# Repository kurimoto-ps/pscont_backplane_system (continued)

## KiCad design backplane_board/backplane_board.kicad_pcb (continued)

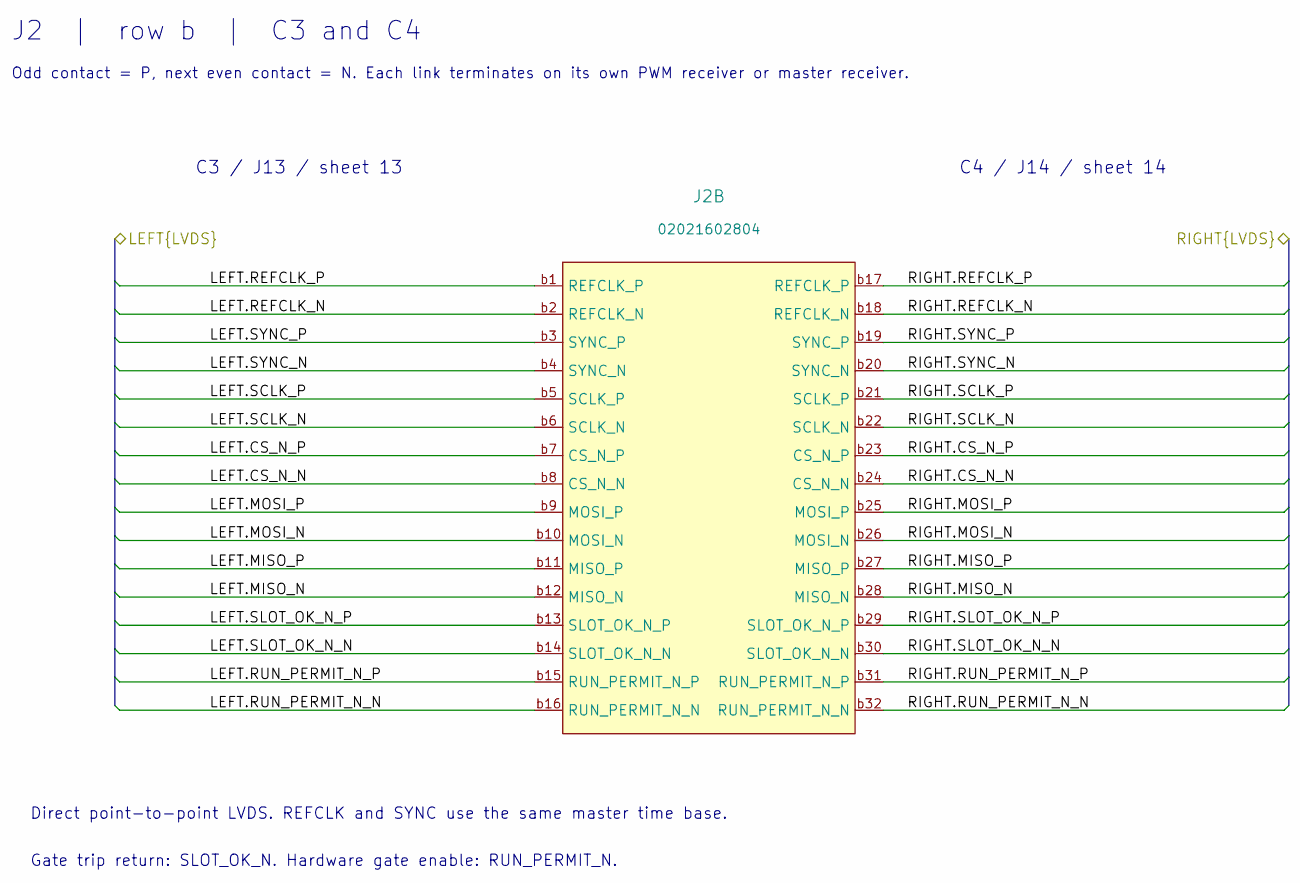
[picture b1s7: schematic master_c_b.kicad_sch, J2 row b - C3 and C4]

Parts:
J2: 02021602804; HARBUS64_02021602804; MPN 02021602804

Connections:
/C3.CS_N_N: J2.b8 (CS_N_N); also elsewhere on the board
/C3.CS_N_P: J2.b7 (CS_N_P); also elsewhere on the board
/C3.MISO_N: J2.b12 (MISO_N); also elsewhere on the board
/C3.MISO_P: J2.b11 (MISO_P); also elsewhere on the board
/C3.MOSI_N: J2.b10 (MOSI_N); also elsewhere on the board
/C3.MOSI_P: J2.b9 (MOSI_P); also elsewhere on the board
/C3.REFCLK_N: J2.b2 (REFCLK_N); also elsewhere on the board
/C3.REFCLK_P: J2.b1 (REFCLK_P); also elsewhere on the board
/C3.RUN_PERMIT_N_N: J2.b16 (RUN_PERMIT_N_N); also elsewhere on the board
/C3.RUN_PERMIT_N_P: J2.b15 (RUN_PERMIT_N_P); also elsewhere on the board
/C3.SCLK_N: J2.b6 (SCLK_N); also elsewhere on the board
/C3.SCLK_P: J2.b5 (SCLK_P); also elsewhere on the board
/C3.SLOT_OK_N_N: J2.b14 (SLOT_OK_N_N); also elsewhere on the board
/C3.SLOT_OK_N_P: J2.b13 (SLOT_OK_N_P); also elsewhere on the board
/C3.SYNC_N: J2.b4 (SYNC_N); also elsewhere on the board
/C3.SYNC_P: J2.b3 (SYNC_P); also elsewhere on the board
/C4.CS_N_N: J2.b24 (CS_N_N); also elsewhere on the board
/C4.CS_N_P: J2.b23 (CS_N_P); also elsewhere on the board
/C4.MISO_N: J2.b28 (MISO_N); also elsewhere on the board
/C4.MISO_P: J2.b27 (MISO_P); also elsewhere on the board
/C4.MOSI_N: J2.b26 (MOSI_N); also elsewhere on the board
/C4.MOSI_P: J2.b25 (MOSI_P); also elsewhere on the board
/C4.REFCLK_N: J2.b18 (REFCLK_N); also elsewhere on the board
/C4.REFCLK_P: J2.b17 (REFCLK_P); also elsewhere on the board
/C4.RUN_PERMIT_N_N: J2.b32 (RUN_PERMIT_N_N); also elsewhere on the board
/C4.RUN_PERMIT_N_P: J2.b31 (RUN_PERMIT_N_P); also elsewhere on the board
/C4.SCLK_N: J2.b22 (SCLK_N); also elsewhere on the board
/C4.SCLK_P: J2.b21 (SCLK_P); also elsewhere on the board
/C4.SLOT_OK_N_N: J2.b30 (SLOT_OK_N_N); also elsewhere on the board
/C4.SLOT_OK_N_P: J2.b29 (SLOT_OK_N_P); also elsewhere on the board
/C4.SYNC_N: J2.b20 (SYNC_N); also elsewhere on the board
/C4.SYNC_P: J2.b19 (SYNC_P); also elsewhere on the board

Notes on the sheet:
J2 | row b | C3 and C4
Odd contact = P, next even contact = N. Each link terminates on its own PWM receiver or master receiver.
C3 / J13 / sheet 13
C4 / J14 / sheet 14
Direct point-to-point LVDS. REFCLK and SYNC use the same master time base.
Gate trip return: SLOT_OK_N. Hardware gate enable: RUN_PERMIT_N.

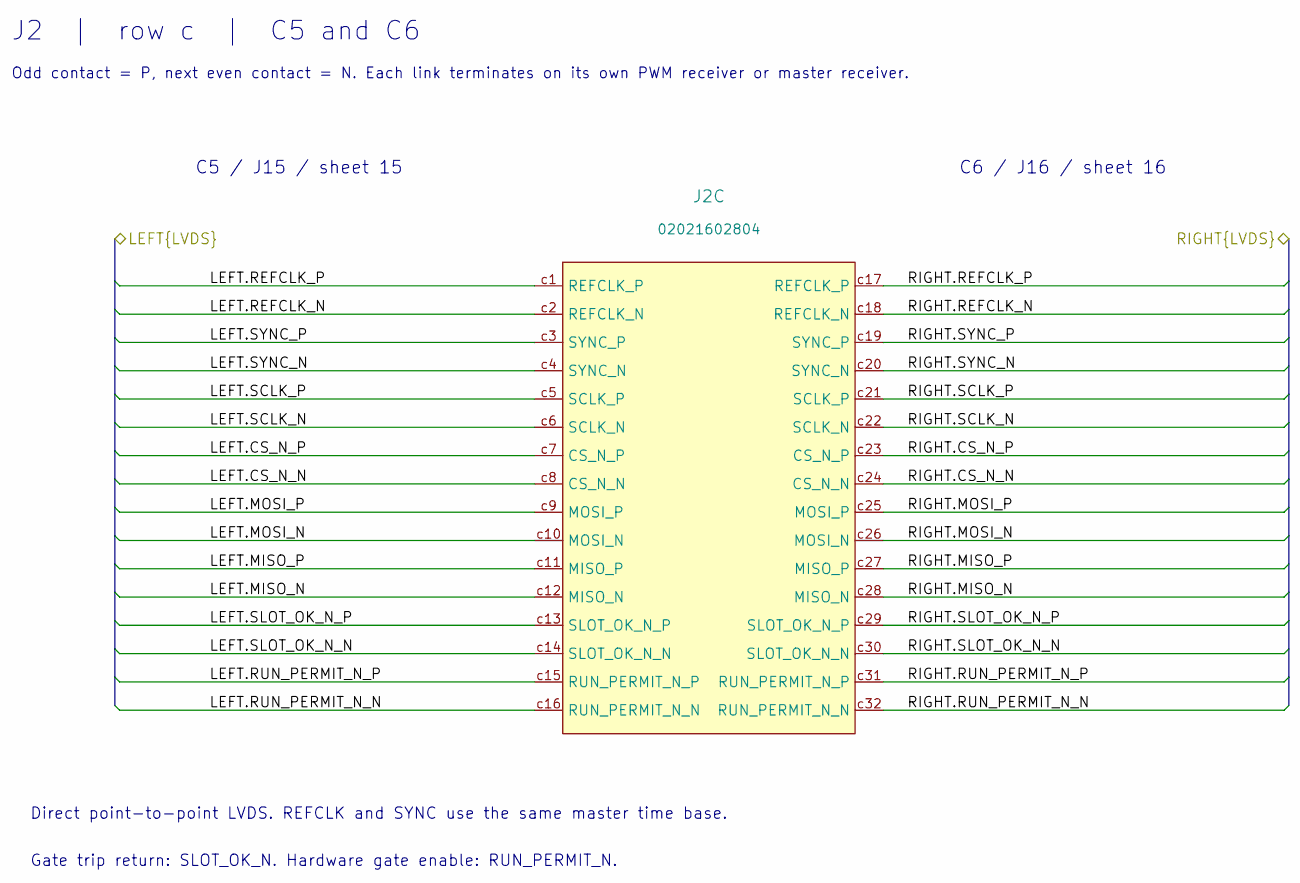
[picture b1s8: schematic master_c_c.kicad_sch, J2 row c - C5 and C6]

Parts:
J2: 02021602804; HARBUS64_02021602804; MPN 02021602804

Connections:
/C5.CS_N_N: J2.c8 (CS_N_N); also elsewhere on the board
/C5.CS_N_P: J2.c7 (CS_N_P); also elsewhere on the board
/C5.MISO_N: J2.c12 (MISO_N); also elsewhere on the board
/C5.MISO_P: J2.c11 (MISO_P); also elsewhere on the board
/C5.MOSI_N: J2.c10 (MOSI_N); also elsewhere on the board
/C5.MOSI_P: J2.c9 (MOSI_P); also elsewhere on the board
/C5.REFCLK_N: J2.c2 (REFCLK_N); also elsewhere on the board
/C5.REFCLK_P: J2.c1 (REFCLK_P); also elsewhere on the board
/C5.RUN_PERMIT_N_N: J2.c16 (RUN_PERMIT_N_N); also elsewhere on the board
/C5.RUN_PERMIT_N_P: J2.c15 (RUN_PERMIT_N_P); also elsewhere on the board
/C5.SCLK_N: J2.c6 (SCLK_N); also elsewhere on the board
/C5.SCLK_P: J2.c5 (SCLK_P); also elsewhere on the board
/C5.SLOT_OK_N_N: J2.c14 (SLOT_OK_N_N); also elsewhere on the board
/C5.SLOT_OK_N_P: J2.c13 (SLOT_OK_N_P); also elsewhere on the board
/C5.SYNC_N: J2.c4 (SYNC_N); also elsewhere on the board
/C5.SYNC_P: J2.c3 (SYNC_P); also elsewhere on the board
/C6.CS_N_N: J2.c24 (CS_N_N); also elsewhere on the board
/C6.CS_N_P: J2.c23 (CS_N_P); also elsewhere on the board
/C6.MISO_N: J2.c28 (MISO_N); also elsewhere on the board
/C6.MISO_P: J2.c27 (MISO_P); also elsewhere on the board
/C6.MOSI_N: J2.c26 (MOSI_N); also elsewhere on the board
/C6.MOSI_P: J2.c25 (MOSI_P); also elsewhere on the board
/C6.REFCLK_N: J2.c18 (REFCLK_N); also elsewhere on the board
/C6.REFCLK_P: J2.c17 (REFCLK_P); also elsewhere on the board
/C6.RUN_PERMIT_N_N: J2.c32 (RUN_PERMIT_N_N); also elsewhere on the board
/C6.RUN_PERMIT_N_P: J2.c31 (RUN_PERMIT_N_P); also elsewhere on the board
/C6.SCLK_N: J2.c22 (SCLK_N); also elsewhere on the board
/C6.SCLK_P: J2.c21 (SCLK_P); also elsewhere on the board
/C6.SLOT_OK_N_N: J2.c30 (SLOT_OK_N_N); also elsewhere on the board
/C6.SLOT_OK_N_P: J2.c29 (SLOT_OK_N_P); also elsewhere on the board
/C6.SYNC_N: J2.c20 (SYNC_N); also elsewhere on the board
/C6.SYNC_P: J2.c19 (SYNC_P); also elsewhere on the board

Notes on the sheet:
J2 | row c | C5 and C6
Odd contact = P, next even contact = N. Each link terminates on its own PWM receiver or master receiver.
C5 / J15 / sheet 15
C6 / J16 / sheet 16
Direct point-to-point LVDS. REFCLK and SYNC use the same master time base.
Gate trip return: SLOT_OK_N. Hardware gate enable: RUN_PERMIT_N.

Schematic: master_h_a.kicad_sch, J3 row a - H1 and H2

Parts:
J3: 02021602804; HARBUS64_02021602804; MPN 02021602804

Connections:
/H1.CS_N_N: J3.a8 (CS_N_N); also elsewhere on the board
/H1.CS_N_P: J3.a7 (CS_N_P); also elsewhere on the board
/H1.MISO_N: J3.a12 (MISO_N); also elsewhere on the board
/H1.MISO_P: J3.a11 (MISO_P); also elsewhere on the board
/H1.MOSI_N: J3.a10 (MOSI_N); also elsewhere on the board
/H1.MOSI_P: J3.a9 (MOSI_P); also elsewhere on the board
/H1.REFCLK_N: J3.a2 (REFCLK_N); also elsewhere on the board
/H1.REFCLK_P: J3.a1 (REFCLK_P); also elsewhere on the board
/H1.RUN_PERMIT_N_N: J3.a16 (RUN_PERMIT_N_N); also elsewhere on the board
/H1.RUN_PERMIT_N_P: J3.a15 (RUN_PERMIT_N_P); also elsewhere on the board
/H1.SCLK_N: J3.a6 (SCLK_N); also elsewhere on the board
/H1.SCLK_P: J3.a5 (SCLK_P); also elsewhere on the board
/H1.SLOT_OK_N_N: J3.a14 (SLOT_OK_N_N); also elsewhere on the board
/H1.SLOT_OK_N_P: J3.a13 (SLOT_OK_N_P); also elsewhere on the board
/H1.SYNC_N: J3.a4 (SYNC_N); also elsewhere on the board
/H1.SYNC_P: J3.a3 (SYNC_P); also elsewhere on the board
/H2.CS_N_N: J3.a24 (CS_N_N); also elsewhere on the board
/H2.CS_N_P: J3.a23 (CS_N_P); also elsewhere on the board
/H2.MISO_N: J3.a28 (MISO_N); also elsewhere on the board
/H2.MISO_P: J3.a27 (MISO_P); also elsewhere on the board
/H2.MOSI_N: J3.a26 (MOSI_N); also elsewhere on the board
/H2.MOSI_P: J3.a25 (MOSI_P); also elsewhere on the board
/H2.REFCLK_N: J3.a18 (REFCLK_N); also elsewhere on the board
/H2.REFCLK_P: J3.a17 (REFCLK_P); also elsewhere on the board
/H2.RUN_PERMIT_N_N: J3.a32 (RUN_PERMIT_N_N); also elsewhere on the board
/H2.RUN_PERMIT_N_P: J3.a31 (RUN_PERMIT_N_P); also elsewhere on the board
/H2.SCLK_N: J3.a22 (SCLK_N); also elsewhere on the board
/H2.SCLK_P: J3.a21 (SCLK_P); also elsewhere on the board
/H2.SLOT_OK_N_N: J3.a30 (SLOT_OK_N_N); also elsewhere on the board
/H2.SLOT_OK_N_P: J3.a29 (SLOT_OK_N_P); also elsewhere on the board
/H2.SYNC_N: J3.a20 (SYNC_N); also elsewhere on the board
/H2.SYNC_P: J3.a19 (SYNC_P); also elsewhere on the board

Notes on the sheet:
J3 | row a | H1 and H2
Odd contact = P, next even contact = N. Each link terminates on its own PWM receiver or master receiver.
H1 / J17 / sheet 17
H2 / J18 / sheet 18
Direct point-to-point LVDS. REFCLK and SYNC use the same master time base.
Gate trip return: SLOT_OK_N. Hardware gate enable: RUN_PERMIT_N.

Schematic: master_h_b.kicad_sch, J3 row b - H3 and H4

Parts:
J3: 02021602804; HARBUS64_02021602804; MPN 02021602804

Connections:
/H3.CS_N_N: J3.b8 (CS_N_N); also elsewhere on the board
/H3.CS_N_P: J3.b7 (CS_N_P); also elsewhere on the board
/H3.MISO_N: J3.b12 (MISO_N); also elsewhere on the board
/H3.MISO_P: J3.b11 (MISO_P); also elsewhere on the board
/H3.MOSI_N: J3.b10 (MOSI_N); also elsewhere on the board
/H3.MOSI_P: J3.b9 (MOSI_P); also elsewhere on the board
/H3.REFCLK_N: J3.b2 (REFCLK_N); also elsewhere on the board
/H3.REFCLK_P: J3.b1 (REFCLK_P); also elsewhere on the board
/H3.RUN_PERMIT_N_N: J3.b16 (RUN_PERMIT_N_N); also elsewhere on the board
/H3.RUN_PERMIT_N_P: J3.b15 (RUN_PERMIT_N_P); also elsewhere on the board
/H3.SCLK_N: J3.b6 (SCLK_N); also elsewhere on the board
/H3.SCLK_P: J3.b5 (SCLK_P); also elsewhere on the board
/H3.SLOT_OK_N_N: J3.b14 (SLOT_OK_N_N); also elsewhere on the board
/H3.SLOT_OK_N_P: J3.b13 (SLOT_OK_N_P); also elsewhere on the board
/H3.SYNC_N: J3.b4 (SYNC_N); also elsewhere on the board
/H3.SYNC_P: J3.b3 (SYNC_P); also elsewhere on the board
/H4.CS_N_N: J3.b24 (CS_N_N); also elsewhere on the board
/H4.CS_N_P: J3.b23 (CS_N_P); also elsewhere on the board
/H4.MISO_N: J3.b28 (MISO_N); also elsewhere on the board
/H4.MISO_P: J3.b27 (MISO_P); also elsewhere on the board
/H4.MOSI_N: J3.b26 (MOSI_N); also elsewhere on the board
/H4.MOSI_P: J3.b25 (MOSI_P); also elsewhere on the board
/H4.REFCLK_N: J3.b18 (REFCLK_N); also elsewhere on the board
/H4.REFCLK_P: J3.b17 (REFCLK_P); also elsewhere on the board
/H4.RUN_PERMIT_N_N: J3.b32 (RUN_PERMIT_N_N); also elsewhere on the board
/H4.RUN_PERMIT_N_P: J3.b31 (RUN_PERMIT_N_P); also elsewhere on the board
/H4.SCLK_N: J3.b22 (SCLK_N); also elsewhere on the board
/H4.SCLK_P: J3.b21 (SCLK_P); also elsewhere on the board
/H4.SLOT_OK_N_N: J3.b30 (SLOT_OK_N_N); also elsewhere on the board
/H4.SLOT_OK_N_P: J3.b29 (SLOT_OK_N_P); also elsewhere on the board
/H4.SYNC_N: J3.b20 (SYNC_N); also elsewhere on the board
/H4.SYNC_P: J3.b19 (SYNC_P); also elsewhere on the board

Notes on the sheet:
J3 | row b | H3 and H4
Odd contact = P, next even contact = N. Each link terminates on its own PWM receiver or master receiver.
H3 / J19 / sheet 19
H4 / J20 / sheet 20
Direct point-to-point LVDS. REFCLK and SYNC use the same master time base.
Gate trip return: SLOT_OK_N. Hardware gate enable: RUN_PERMIT_N.

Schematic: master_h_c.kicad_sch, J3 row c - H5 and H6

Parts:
J3: 02021602804; HARBUS64_02021602804; MPN 02021602804

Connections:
/H5.CS_N_N: J3.c8 (CS_N_N); also elsewhere on the board
/H5.CS_N_P: J3.c7 (CS_N_P); also elsewhere on the board
/H5.MISO_N: J3.c12 (MISO_N); also elsewhere on the board
/H5.MISO_P: J3.c11 (MISO_P); also elsewhere on the board
/H5.MOSI_N: J3.c10 (MOSI_N); also elsewhere on the board
/H5.MOSI_P: J3.c9 (MOSI_P); also elsewhere on the board
/H5.REFCLK_N: J3.c2 (REFCLK_N); also elsewhere on the board
/H5.REFCLK_P: J3.c1 (REFCLK_P); also elsewhere on the board
/H5.RUN_PERMIT_N_N: J3.c16 (RUN_PERMIT_N_N); also elsewhere on the board
/H5.RUN_PERMIT_N_P: J3.c15 (RUN_PERMIT_N_P); also elsewhere on the board
/H5.SCLK_N: J3.c6 (SCLK_N); also elsewhere on the board
/H5.SCLK_P: J3.c5 (SCLK_P); also elsewhere on the board
/H5.SLOT_OK_N_N: J3.c14 (SLOT_OK_N_N); also elsewhere on the board
/H5.SLOT_OK_N_P: J3.c13 (SLOT_OK_N_P); also elsewhere on the board
/H5.SYNC_N: J3.c4 (SYNC_N); also elsewhere on the board
/H5.SYNC_P: J3.c3 (SYNC_P); also elsewhere on the board
/H6.CS_N_N: J3.c24 (CS_N_N); also elsewhere on the board
/H6.CS_N_P: J3.c23 (CS_N_P); also elsewhere on the board
/H6.MISO_N: J3.c28 (MISO_N); also elsewhere on the board
/H6.MISO_P: J3.c27 (MISO_P); also elsewhere on the board
/H6.MOSI_N: J3.c26 (MOSI_N); also elsewhere on the board
/H6.MOSI_P: J3.c25 (MOSI_P); also elsewhere on the board
/H6.REFCLK_N: J3.c18 (REFCLK_N); also elsewhere on the board
/H6.REFCLK_P: J3.c17 (REFCLK_P); also elsewhere on the board
/H6.RUN_PERMIT_N_N: J3.c32 (RUN_PERMIT_N_N); also elsewhere on the board
/H6.RUN_PERMIT_N_P: J3.c31 (RUN_PERMIT_N_P); also elsewhere on the board
/H6.SCLK_N: J3.c22 (SCLK_N); also elsewhere on the board
/H6.SCLK_P: J3.c21 (SCLK_P); also elsewhere on the board
/H6.SLOT_OK_N_N: J3.c30 (SLOT_OK_N_N); also elsewhere on the board
/H6.SLOT_OK_N_P: J3.c29 (SLOT_OK_N_P); also elsewhere on the board
/H6.SYNC_N: J3.c20 (SYNC_N); also elsewhere on the board
/H6.SYNC_P: J3.c19 (SYNC_P); also elsewhere on the board

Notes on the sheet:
J3 | row c | H5 and H6
Odd contact = P, next even contact = N. Each link terminates on its own PWM receiver or master receiver.
H5 / J21 / sheet 21
H6 / J22 / sheet 22
Direct point-to-point LVDS. REFCLK and SYNC use the same master time base.
Gate trip return: SLOT_OK_N. Hardware gate enable: RUN_PERMIT_N.

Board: 6 copper layers, 101 parts (33 on the bottom side), 210 nets, no tracks yet.

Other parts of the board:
MH1, MH2, MH3, MH4, MH5, MH6, MH7, MH8, MH9, MH10, MH11, MH12, MH13, MH14, MH15, MH16, MH17, MH18, MH19, MH20, MH21, MH22: 2.7mm_M2.5; MountingHole_2.7mm_M2.5
MH23, MH24, MH25, MH26, MH27, MH28, MH29, MH30, MH31, MH32, MH33, MH34, MH35, MH36, MH37, MH38, MH39, MH40, MH41, MH42, MH43, MH44, MH45, MH46, MH47, MH48, MH49, MH50, MH51, MH52, MH53, MH54: 3.2mm_M3; MountingHole_3.2mm_M3
